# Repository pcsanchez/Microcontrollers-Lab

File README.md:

# Microcontrollers-Lab
Code and Design for micro controllers class and lab

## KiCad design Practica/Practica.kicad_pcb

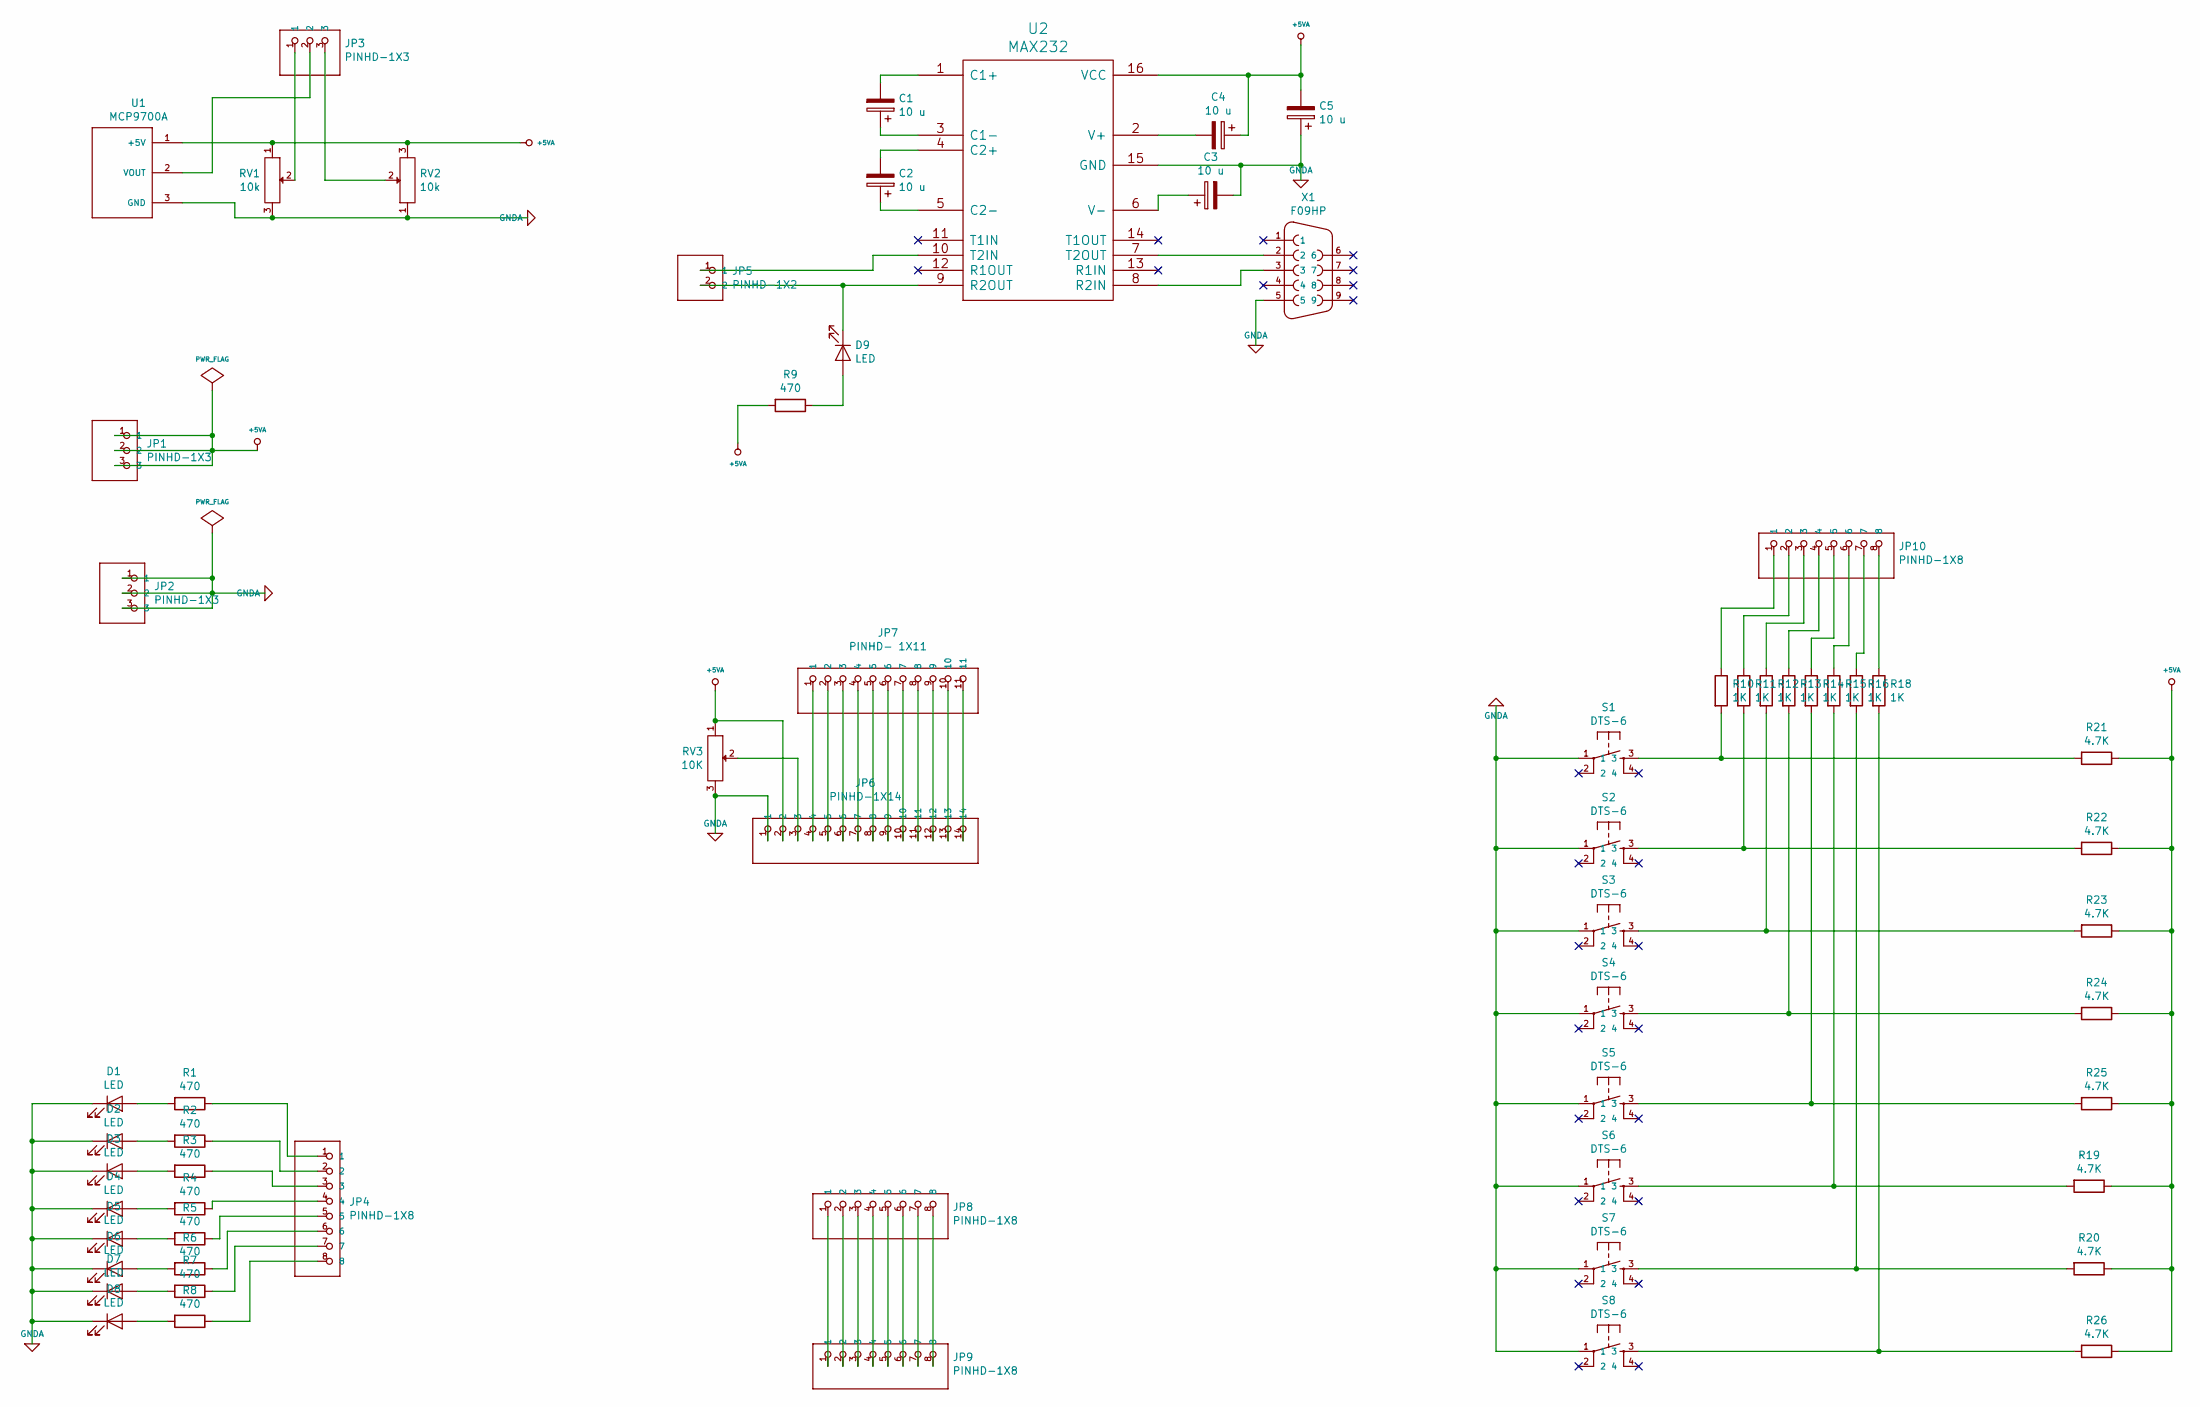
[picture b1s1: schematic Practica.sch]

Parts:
C1, C2, C3, C4, C5: 10 u; Capacitor_elect
D1, D2, D3, D4, D5, D6, D7, D8, D9: LED; Led
JP1, JP2, JP3: PINHD-1X3; pinhead-1X03
JP4, JP8, JP9, JP10: PINHD-1X8; pinhead-1X08
JP5: PINHD-1X2; pinhead-1X02
JP6: PINHD-1X14; pinhead-1X14
JP7: PINHD- 1X11; pinhead-1X11
R1, R2, R3, R4, R5, R6, R7, R8: 470; Resistor
R9: 470; Resistor_large
R10, R11, R12, R13, R14, R15, R16, R18: 1K; Resistor
R19, R20, R21, R22, R23, R24, R25, R26: 4.7K; Resistor
RV1, RV2: 10k; RV2X4
RV3: 10K; RV2X4
S1, S2, S3, S4, S5, S6, S7, S8: DTS-6
U1: MCP9700A
U2: MAX232; Maxim232
X1: F09HP; Conector_F09HP

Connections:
+5VA: C4.1, C5.2, JP1.1, JP1.2, JP1.3, JP6.2, R9.2, R19.1, R20.1, R21.1, R22.1, R23.1, R24.1, R25.1, R26.1, RV1.1, RV2.3, RV3.1, U1.1 (+5V), U2.16 (VCC)
GNDA: C3.2, C5.1, D1.1 (K), D2.1 (K), D3.1 (K), D4.1 (K), D5.1 (K), D6.1 (K), D7.1 (K), D8.1 (K), JP2.1, JP2.2, JP2.3, JP6.1, RV1.3, RV2.1, RV3.3, S1.1, S2.1, S3.1, S4.1, S5.1, S6.1, S7.1, S8.1, U1.3 (GND), U2.15 (GND), X1.5
unnamed: C1.1, U2.3 (C1-)
unnamed: C1.2, U2.1 (C1+)
unnamed: C2.1, U2.5 (C2-)
unnamed: C2.2, U2.4 (C2+)
unnamed: C3.1, U2.6 (V-)
unnamed: C4.2, U2.2 (V+)
unnamed: D1.2 (A), R1.2
unnamed: D2.2 (A), R2.2
unnamed: D3.2 (A), R3.2
unnamed: D4.2 (A), R4.2
unnamed: D5.2 (A), R5.2
unnamed: D6.2 (A), R6.2
unnamed: D7.2 (A), R7.2
unnamed: D8.2 (A), R8.2
unnamed: D9.1 (K), JP5.2, U2.9 (R2OUT)
unnamed: D9.2 (A), R9.1
unnamed: JP3.1, RV1.2
unnamed: JP3.2, U1.2 (VOUT)
unnamed: JP3.3, RV2.2
unnamed: JP4.1, R1.1
unnamed: JP4.2, R2.1
unnamed: JP4.3, R3.1
unnamed: JP4.4, R4.1
unnamed: JP4.5, R5.1
unnamed: JP4.6, R6.1
unnamed: JP4.7, R7.1
unnamed: JP4.8, R8.1
unnamed: JP5.1, U2.10 (T2IN)
unnamed: JP6.3, RV3.2
unnamed: JP6.4, JP7.1
unnamed: JP6.5, JP7.2
unnamed: JP6.6, JP7.3
unnamed: JP6.7, JP7.4
unnamed: JP6.8, JP7.5
unnamed: JP6.9, JP7.6
unnamed: JP6.10, JP7.7
unnamed: JP6.11, JP7.8
unnamed: JP6.12, JP7.9
unnamed: JP6.13, JP7.10
unnamed: JP6.14, JP7.11
unnamed: JP8.1, JP9.1
unnamed: JP8.2, JP9.2
unnamed: JP8.3, JP9.3
unnamed: JP8.4, JP9.4
unnamed: JP8.5, JP9.5
unnamed: JP8.6, JP9.6
unnamed: JP8.7, JP9.7
unnamed: JP8.8, JP9.8
unnamed: JP10.1, R10.1
unnamed: JP10.2, R11.1
unnamed: JP10.3, R12.1
unnamed: JP10.4, R13.1
unnamed: JP10.5, R14.1
unnamed: JP10.6, R15.1
unnamed: JP10.7, R16.1
unnamed: JP10.8, R18.1
unnamed: R10.2, R21.2, S1.3
unnamed: R11.2, R22.2, S2.3
unnamed: R12.2, R23.2, S3.3
unnamed: R13.2, R24.2, S4.3
unnamed: R14.2, R25.2, S5.3
unnamed: R15.2, R19.2, S6.3
unnamed: R16.2, R20.2, S7.3
unnamed: R18.2, R26.2, S8.3
unnamed: U2.7 (T2OUT), X1.2
unnamed: U2.8 (R2IN), X1.3

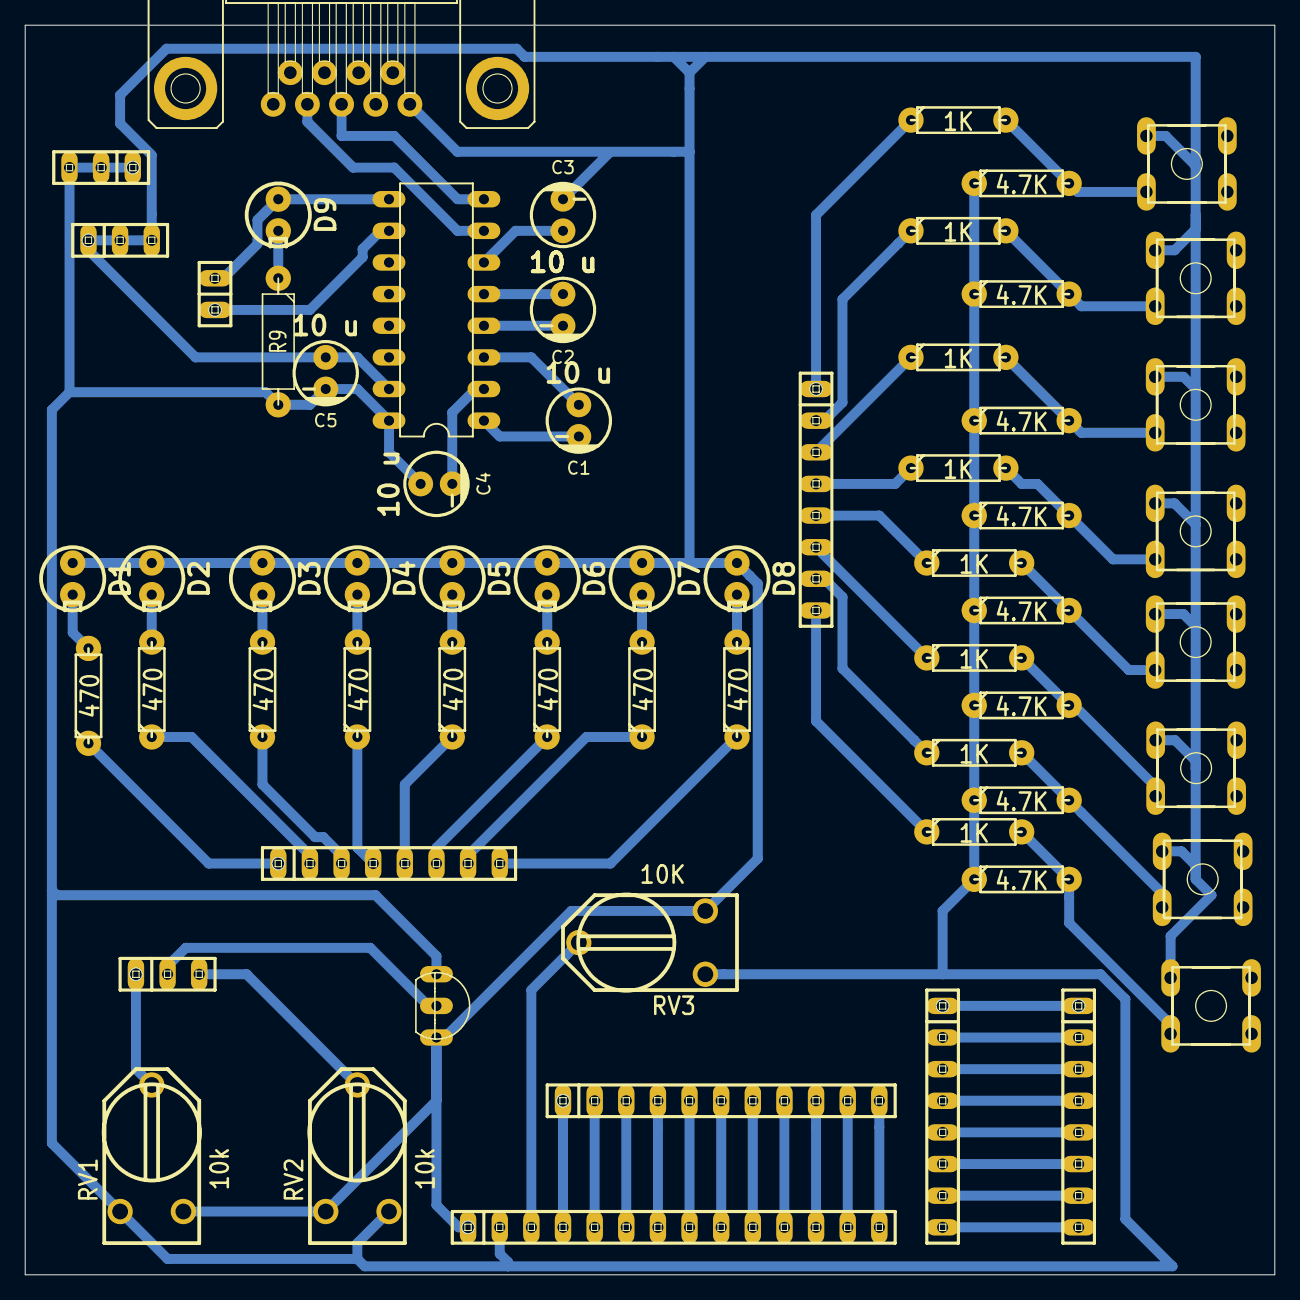
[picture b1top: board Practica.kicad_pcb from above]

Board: 2 copper layers, 100.3 x 100.3 mm, 63 parts (0 on the bottom side), 68 nets.

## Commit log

2019-11-26 pls pass
